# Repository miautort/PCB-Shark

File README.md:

This is a simple project given as an assignment. The conditions were for the board to be within 100x100mm, and to use the specified microprocessor. 

The task itself was to draw something with LEDs. As just placing some LEDs was just boring, I decided to make it interesting through shape as well, and use the components themselves to make it look better. The rat with pink bow meme exploded just about in time to inspire me, so here we are, with a shark with a pink shiny bow.

Here's the component list:

| Component  | Number and/or Type |
| ------------- | ------------- |
| Microcontroller  | MSP430G2553IN20 (U1) | 
| LED  | 12* ; both 3mm and 5mm are compatible    |
| Capacitors | 1x1nF (C1) ; 1x10uF (C3) ; 1x22uF (C2) |
| Connectors | Micro-USB for power (J2) ; 4-pin for programming (J1) |
| Resistors | 1x100kOhm (R1) ; 6x330** Ohm |
| Quartz Crystal | 32kHz (Y1) |
| Voltage Regulator | TLV1117-33 (U2) |

*I used 10 pink for the bow and 2 blue for the eye

**The resistor values depend on the chosen LED color

Below is a screenshot of the electric circuit itself; below that the PCB design, first without ground plan, then with.

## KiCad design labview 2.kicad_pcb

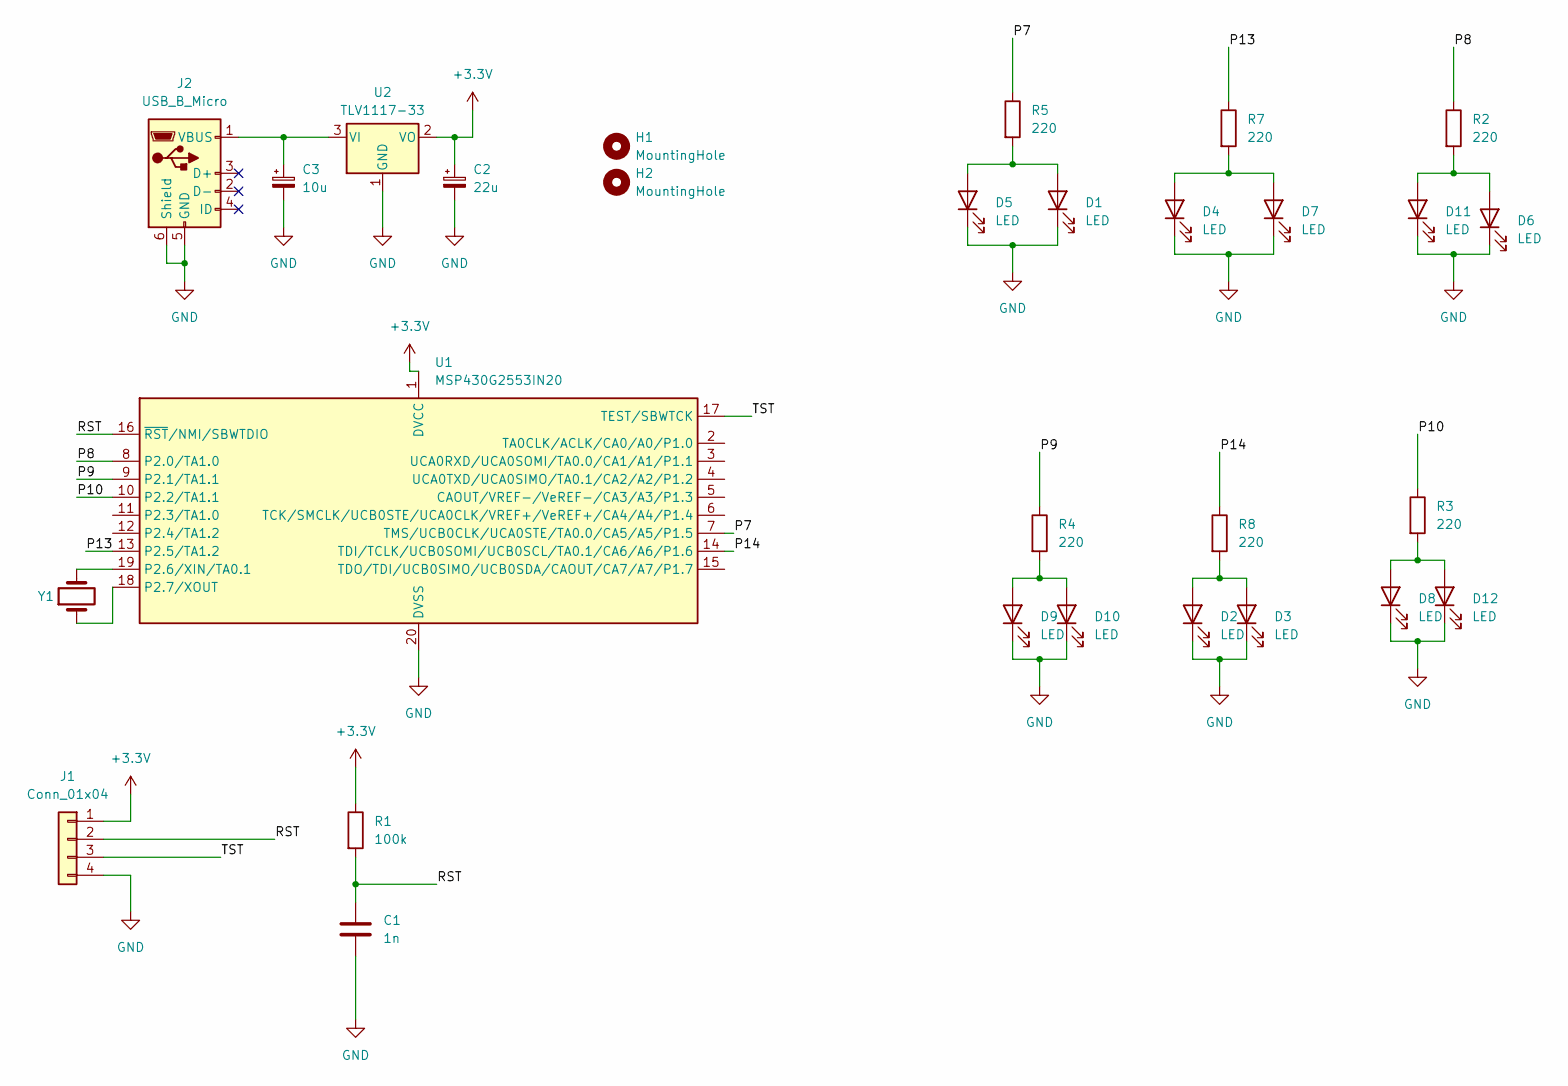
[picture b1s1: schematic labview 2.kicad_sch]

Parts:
C1: 1n; C_Disc_D7.5mm_W5.0mm_P7.50mm
C2: 22u; CP_Radial_D6.3mm_P2.50mm
C3: 10u; CP_Radial_D6.3mm_P2.50mm
D1, D2, D3, D4, D5, D6, D7, D8, D9, D10, D12: LED; LED_D3.0mm
D11: LED; LED_D5.0mm
H1, H2: MountingHole; MountingHole_2.2mm_M2
J1: Conn_01x04; PinHeader_1x04_P2.54mm_Vertical
J2: USB_B_Micro; USB_Micro-B_Wuerth_614105150721_Vertical_CircularHoles
R1: 100k; R_Axial_DIN0207_L6.3mm_D2.5mm_P10.16mm_Horizontal
R2, R3, R4, R5, R7, R8: 220; R_Axial_DIN0207_L6.3mm_D2.5mm_P10.16mm_Horizontal
U1: MSP430G2553IN20; DIP-20_W7.62mm
U2: TLV1117-33; TO-220-3_Vertical
Y1: 32kHz; Crystal_C38-LF_D3.0mm_L8.0mm_Vertical

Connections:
+3.3V: C2.1, J1.1, R1.1, U1.1 (DVCC), U2.2 (VO)
/P1.0: U1.2 (TA0CLK/ACLK/CA0/A0/P1.0)
/P7: R5.1, U1.7 (TMS/UCB0CLK/UCA0STE/TA0.0/CA5/A5/P1.5)
/P8: R2.1, U1.8 (P2.0/TA1.0)
/P9: R4.1, U1.9 (P2.1/TA1.1)
/P10: R3.1, U1.10 (P2.2/TA1.1)
/P12: U1.12 (P2.4/TA1.2)
/P13: R7.1, U1.13 (P2.5/TA1.2)
/P14: R8.1, U1.14 (TDI/TCLK/UCB0SOMI/UCB0SCL/TA0.1/CA6/A6/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)
/P 2.0: U1.3 (UCA0RXD/UCA0SOMI/TA0.0/CA1/A1/P1.1)
/P 3.0: U1.4 (UCA0TXD/UCA0SIMO/TA0.1/CA2/A2/P1.2)
/P 4.0: U1.5 (CAOUT/VREF-/VeREF-/CA3/A3/P1.3)
/P 5.0: U1.6 (TCK/SMCLK/UCB0STE/UCA0CLK/VREF+/VeREF+/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)
/RST: C1.1, J1.2, R1.2, U1.16 (~RST/NMI/SBWTDIO)
/TST: J1.3, U1.17 (TEST/SBWTCK)
GND: C1.2, C2.2, C3.2, D1.1 (K), D2.1 (K), D3.1 (K), D4.1 (K), D5.1 (K), D6.1 (K), D7.1 (K), D8.1 (K), D9.1 (K), D10.1 (K), D11.1 (K), D12.1 (K), J1.4, J2.5 (GND), J2.6 (Shield), U1.20 (DVSS), U2.1 (GND)
unnamed: D1.2 (A), D5.2 (A), R5.2
unnamed: D2.2 (A), D3.2 (A), R8.2
unnamed: D4.2 (A), D7.2 (A), R7.2
unnamed: D9.2 (A), D10.2 (A), R4.2
unnamed: D6.2 (A), D11.2 (A), R2.2
unnamed: D8.2 (A), D12.2 (A), R3.2
unnamed: C3.1, J2.1 (VBUS), U2.3 (VI)
unnamed: U1.19 (P2.6/XIN/TA0.1), Y1.2
unnamed: U1.18 (P2.7/XOUT), Y1.1

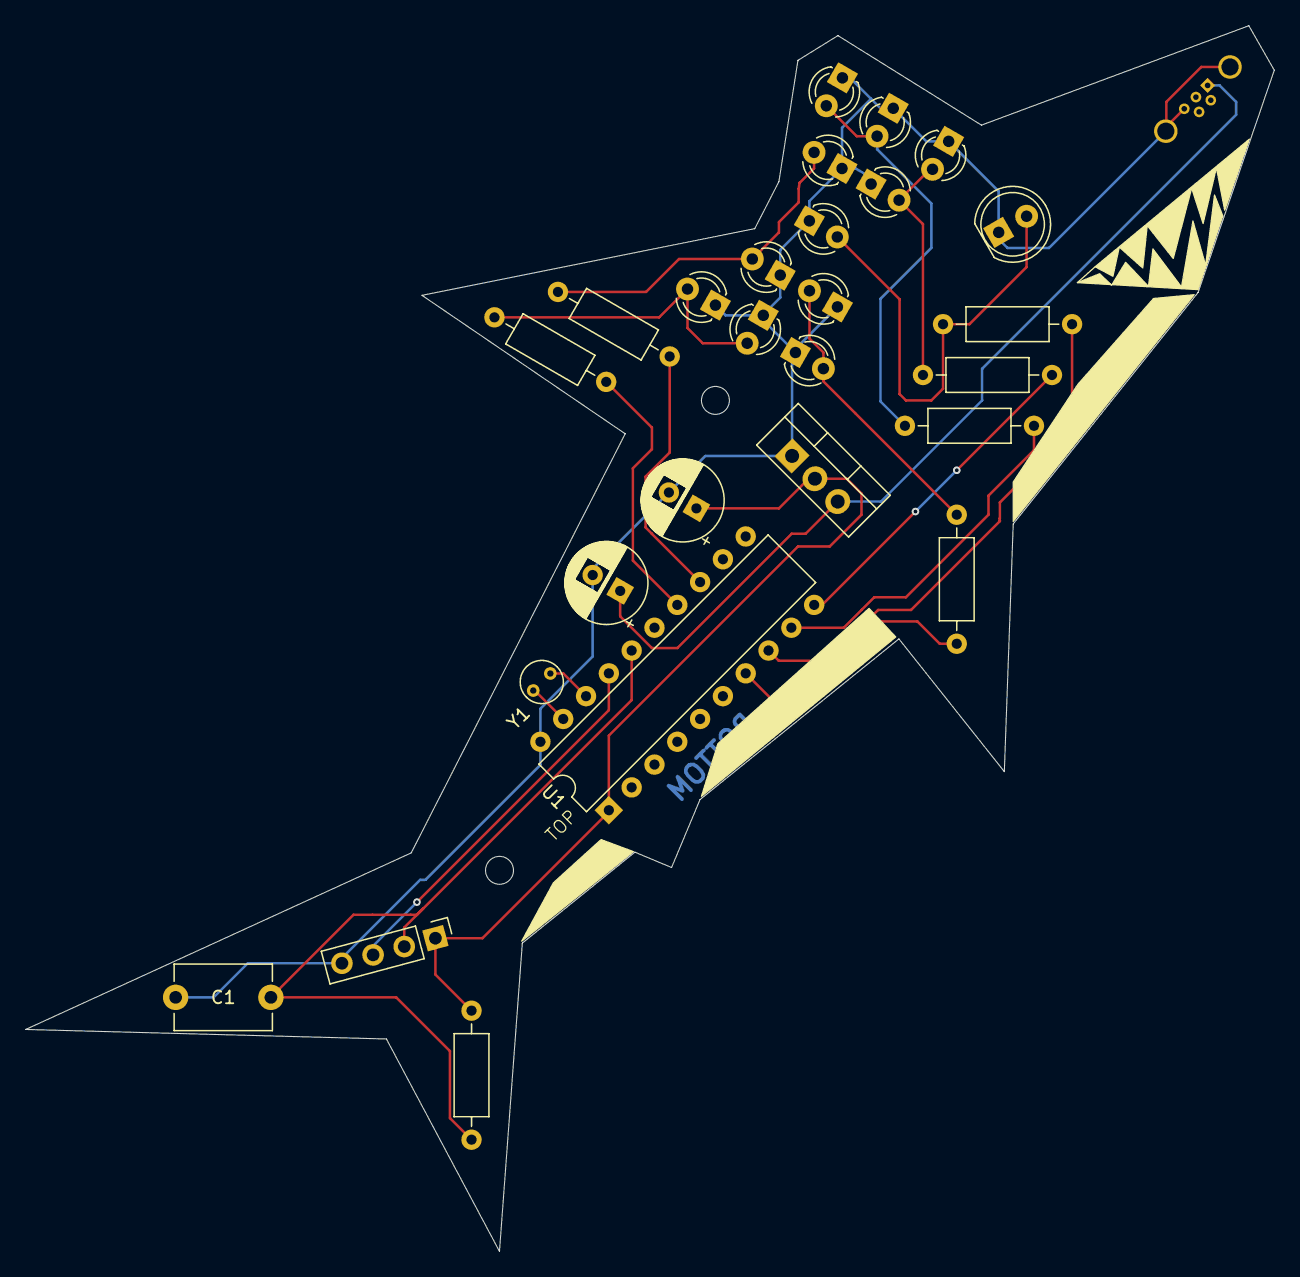
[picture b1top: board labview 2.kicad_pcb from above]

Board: 2 copper layers, 98.3 x 96.5 mm, 29 parts (1 on the bottom side), 19 nets.

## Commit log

2025-12-25 updated readme
    Added project description, component list, and images.
2025-12-25 added kikad files
2025-12-25 Update README.md
    fixed typo
